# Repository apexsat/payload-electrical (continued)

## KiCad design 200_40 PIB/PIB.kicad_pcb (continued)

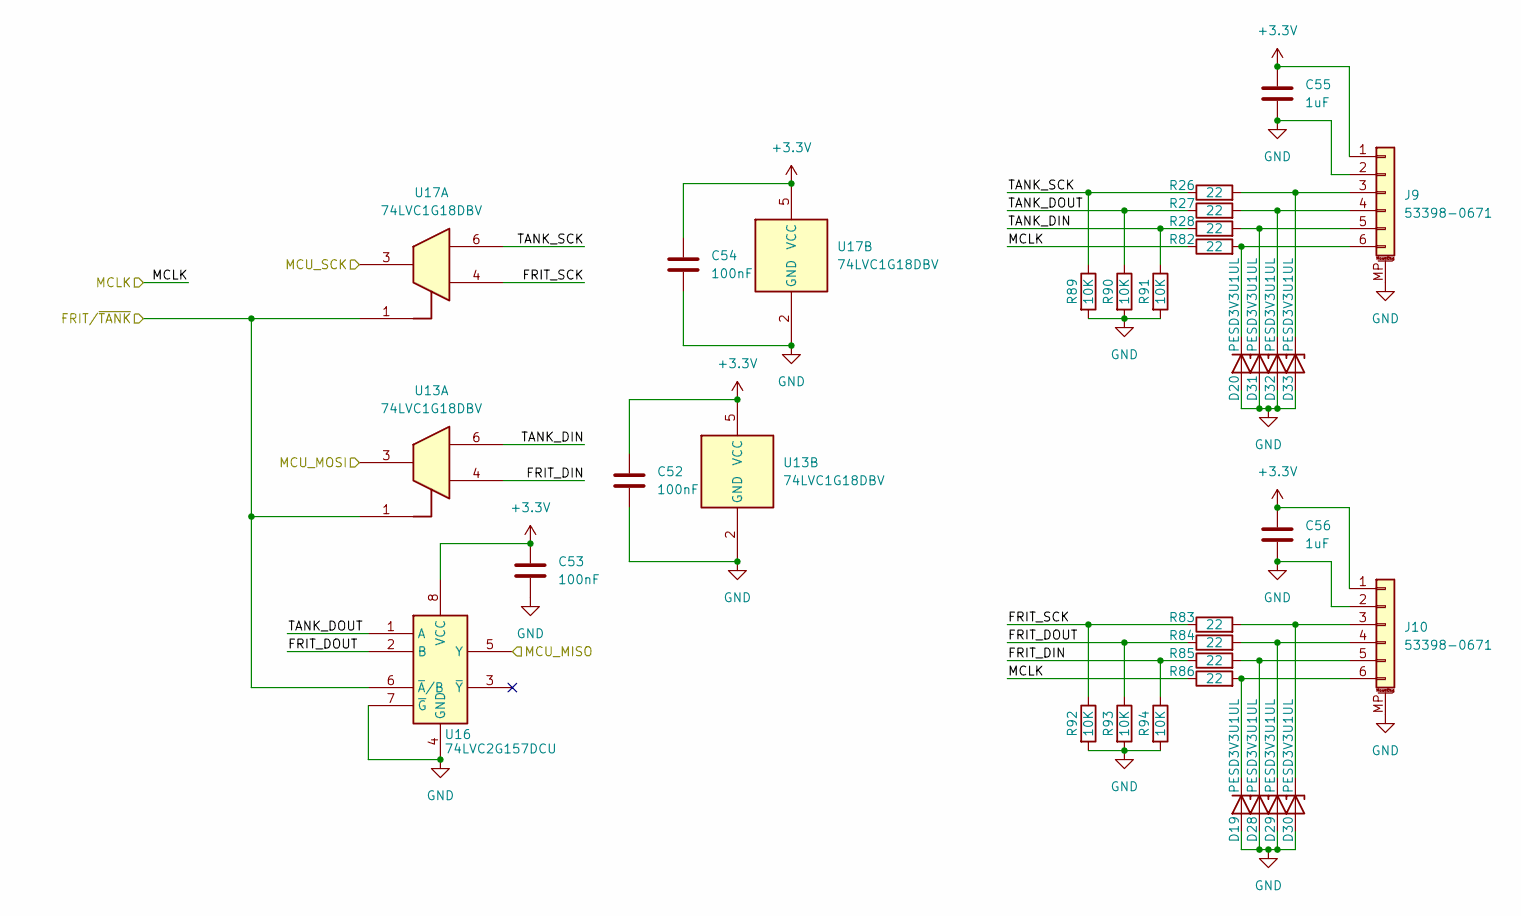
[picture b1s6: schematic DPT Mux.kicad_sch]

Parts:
C52, C53, C54: 100nF; C_0402_1005Metric; Digikey PN 490-10672-1-ND
C55, C56: 1uF; C_0603_1608Metric; Digikey PN 587-3352-1-ND
D19, D20, D28, D29, D30, D31, D32, D33: PESD3V3U1UL; D_SOD-882; Digikey PN 1727-4154-1-ND
J9, J10: 53398-0671; Molex_PicoBlade_53398-0671_1x06-1MP_P1.25mm_Vertical; Digikey PN WM7610CT-ND
R26, R27, R28, R82, R83, R84, R85, R86: 22; R_0402_1005Metric; Digikey PN 311-22.0LRCT-ND
R89, R90, R91, R92, R93, R94: 10K; R_0402_1005Metric; Digikey PN YAG1346CT-ND
U13, U17: 74LVC1G18DBV; SOT-23-6; Digikey PN 296-15568-1-ND
U16: 74LVC2G157DCU; VSSOP-8_2.3x2mm_P0.5mm; Digikey PN 296-12605-1-ND

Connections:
+3.3V: C52.1, C53.1, C54.1, C55.1, C56.1, J9.1, J10.1, U13.5 (VCC), U16.8 (VCC), U17.5 (VCC); also elsewhere on the board
/DPT MUX/FRIT_DIN: R85.1, R94.1, U13.4
/DPT MUX/FRIT_DOUT: R84.1, R93.1, U16.2 (B)
/DPT MUX/FRIT_SCK: R83.1, R92.1, U17.4
/DPT MUX/TANK_DIN: R28.1, R91.1, U13.6
/DPT MUX/TANK_DOUT: R27.1, R90.1, U16.1 (A)
/DPT MUX/TANK_SCK: R26.1, R89.1, U17.6
/DPT_MCLK: R82.1, R86.1; also elsewhere on the board
/FRIT/~TANK: U13.1, U16.6 (~A/B), U17.1; also elsewhere on the board
/INT_SPI_MISO: U16.5 (Y); also elsewhere on the board
/INT_SPI_MOSI: U13.3; also elsewhere on the board
/INT_SPI_SCK: U17.3; also elsewhere on the board
GND: C52.2, C53.2, C54.2, C55.2, C56.2, D19.2 (A), D20.2 (A), D28.2 (A), D29.2 (A), D30.2 (A), D31.2 (A), D32.2 (A), D33.2 (A), J9.2, J9.MP (MountPin), J10.2, J10.MP (MountPin), R89.2, R90.2, R91.2, R92.2, R93.2, R94.2, U13.2 (GND), U16.4 (GND), U16.7 (~G), U17.2 (GND); also elsewhere on the board
unnamed: D19.1 (K), J10.6, R86.2
unnamed: D20.1 (K), J9.6, R82.2
unnamed: D28.1 (K), J10.5, R85.2
unnamed: D29.1 (K), J10.4, R84.2
unnamed: D30.1 (K), J10.3, R83.2
unnamed: D31.1 (K), J9.5, R28.2
unnamed: D32.1 (K), J9.4, R27.2
unnamed: D33.1 (K), J9.3, R26.2

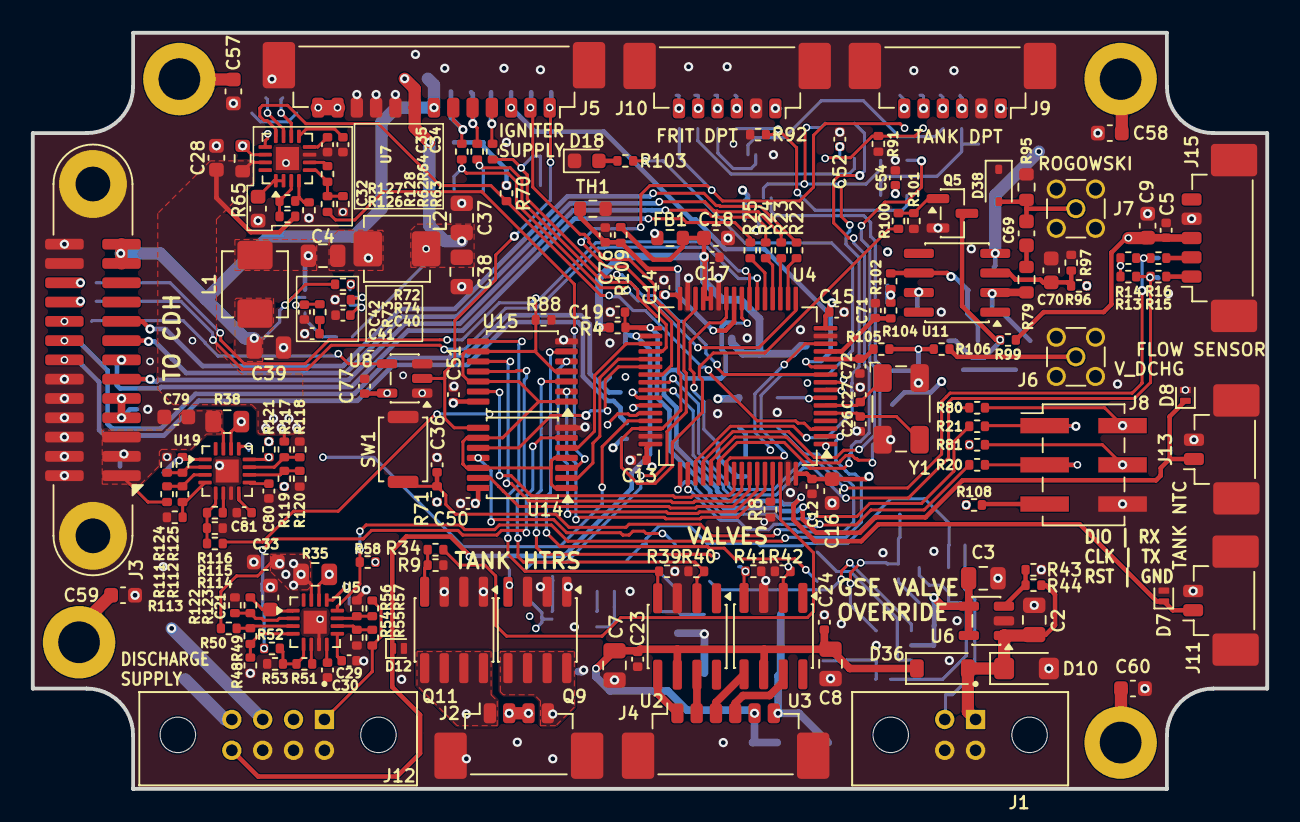
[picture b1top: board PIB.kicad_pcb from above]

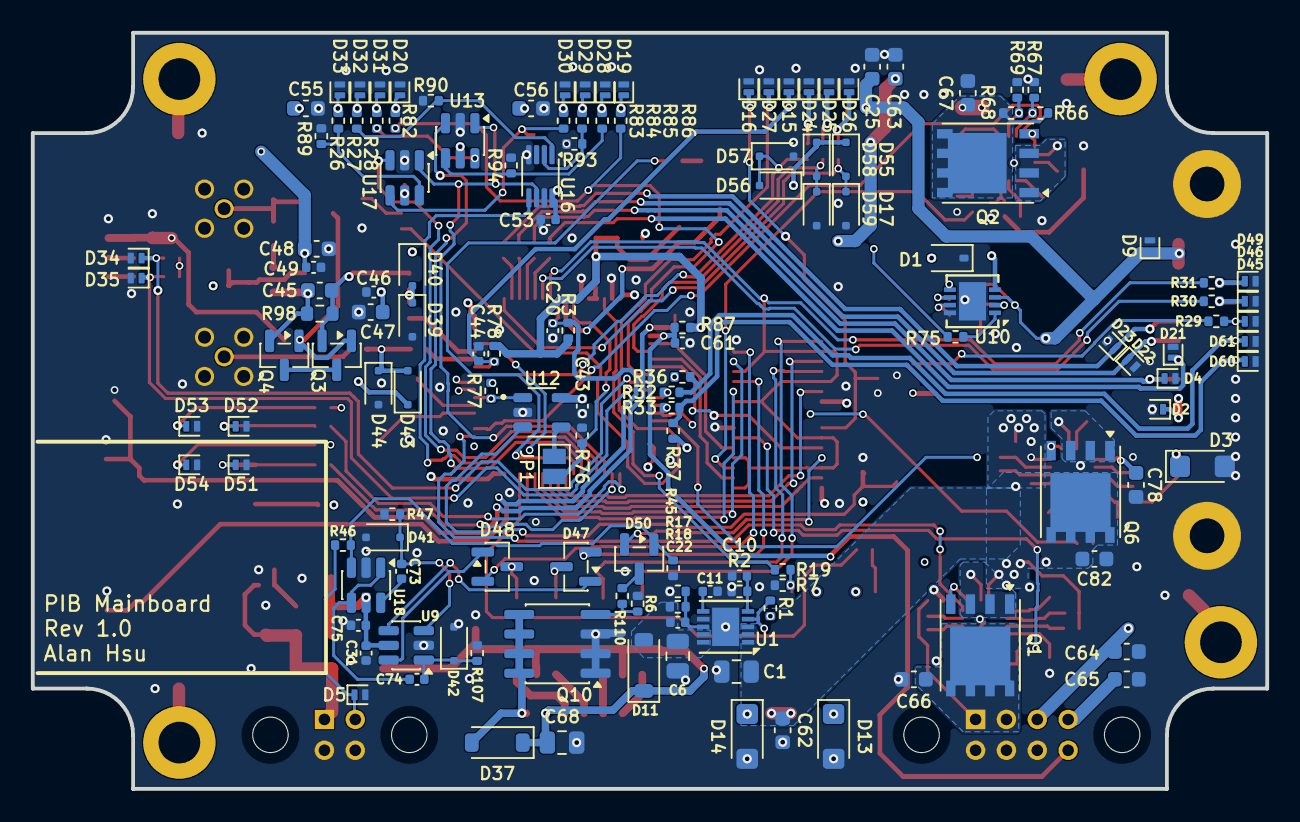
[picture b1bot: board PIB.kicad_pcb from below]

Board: 4 copper layers, 80.0 x 49.0 mm, 319 parts (141 on the bottom side), 192 nets.

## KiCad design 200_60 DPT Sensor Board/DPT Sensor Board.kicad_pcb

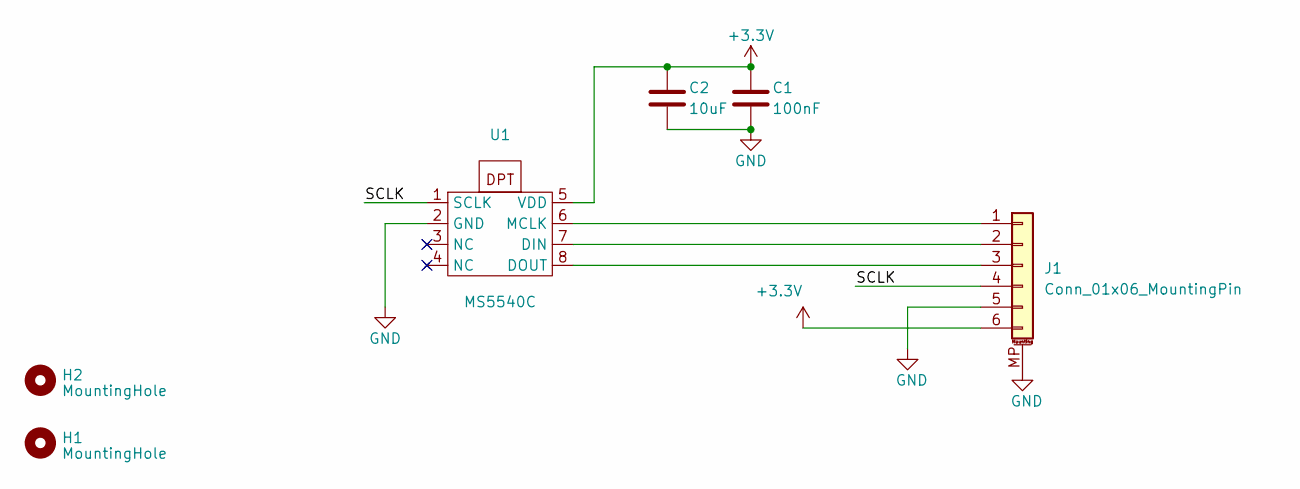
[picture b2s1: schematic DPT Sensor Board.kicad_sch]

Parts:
C1: 100nF; C_0603_1608Metric
C2: 10uF; C_0805_2012Metric
H1, H2: MountingHole; MountingHole_2.1mm
J1: Conn_01x06_MountingPin; Molex_PicoBlade_53261-0671_1x06-1MP_P1.25mm_Horizontal
U1: MS5540C; MPN 325540009-50

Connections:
+3.3V: C1.1, C2.1, J1.6, U1.5 (VDD)
/SCLK: J1.4, U1.1 (SCLK)
GND: C1.2, C2.2, J1.5, J1.MP (MountPin), U1.2 (GND)
unnamed: J1.1, U1.6 (MCLK)
unnamed: J1.2, U1.7 (DIN)
unnamed: J1.3, U1.8 (DOUT)

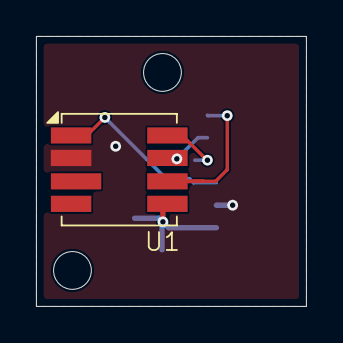
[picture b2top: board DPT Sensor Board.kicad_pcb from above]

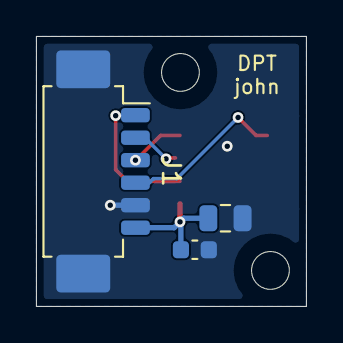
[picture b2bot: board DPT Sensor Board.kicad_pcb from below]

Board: 2 copper layers, 15.0 x 15.0 mm, 6 parts (3 on the bottom side), 6 nets.

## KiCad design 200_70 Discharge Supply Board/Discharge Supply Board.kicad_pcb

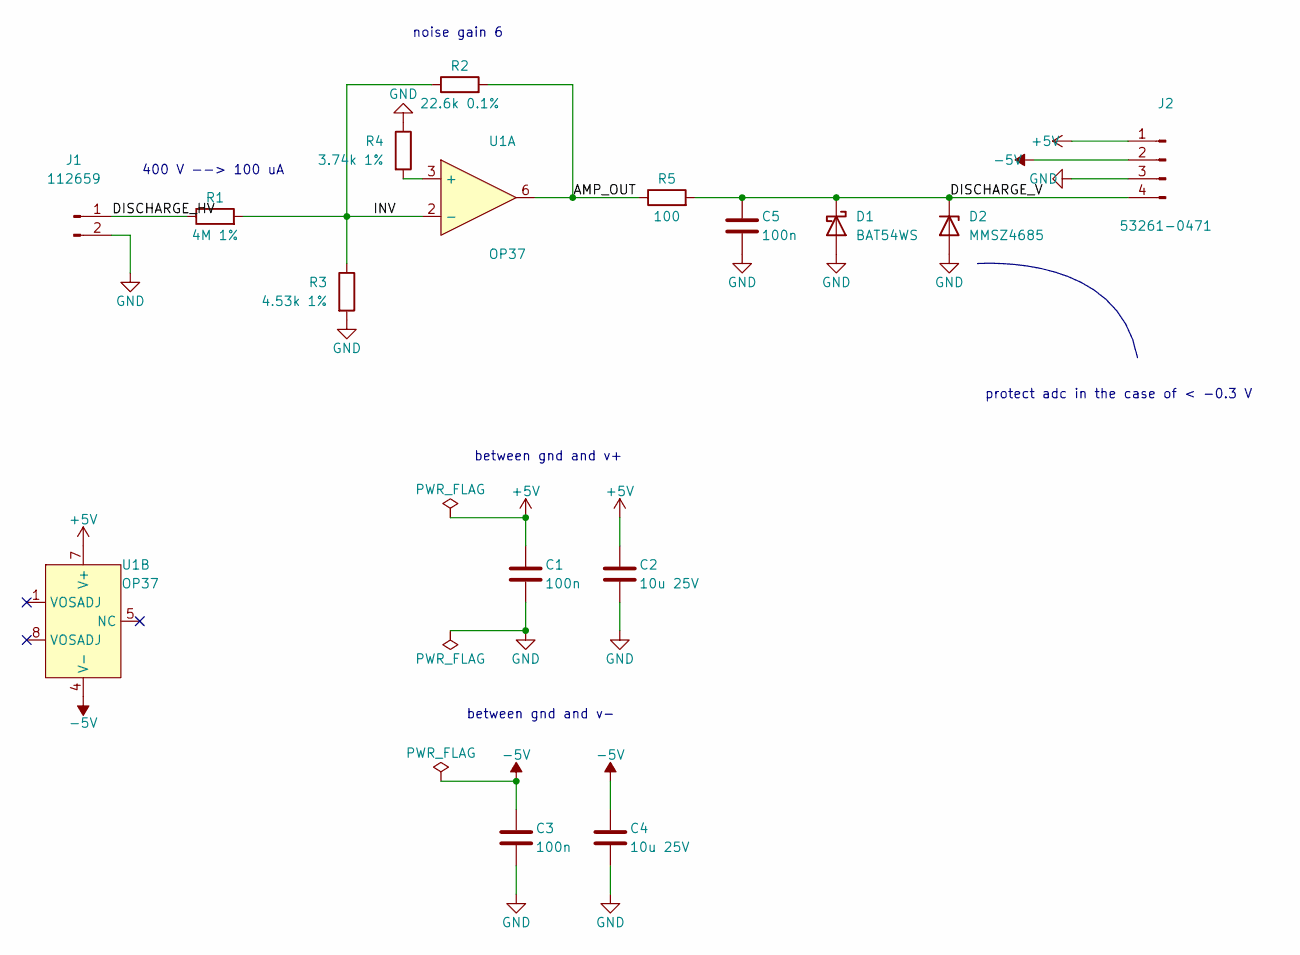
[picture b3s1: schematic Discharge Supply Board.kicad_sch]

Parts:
C1, C3, C5: 100n; C_0603_1608Metric
C2, C4: 10u 25V; C_0805_2012Metric
D1: BAT54WS; D_SOD-323
D2: MMSZ4685; D_SOD-123
J1: 112659; CONN_112659
J2: 53261-0471; Molex_PicoBlade_53261-0471_1x04-1MP_P1.25mm_Horizontal
R1: 4M 1%; R_2512_6332Metric
R2: 22.6k 0.1%; R_0603_1608Metric
R3: 4.53k 1%; R_0603_1608Metric
R4: 3.74k 1%; R_0603_1608Metric
R5: 100; R_0603_1608Metric
U1: OP37; SOIC-8_3.9x4.9mm_P1.27mm

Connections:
+5V: C1.1, C2.1, J2.1, U1.7 (V+)
-5V: C3.1, C4.1, J2.2, U1.4 (V-)
/AMP_OUT: R2.2, R5.1, U1.6
/DISCHARGE_HV: J1.1, R1.1
/DISCHARGE_V: C5.1, D1.1 (K), D2.1 (K), J2.4, R5.2
/INV: R1.2, R2.1, R3.1, U1.2 (-)
GND: C1.2, C2.2, C3.2, C4.2, C5.2, D1.2 (A), D2.2 (A), J1.2, J2.3, R3.2, R4.1
unnamed: R4.2, U1.3 (+)

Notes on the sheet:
protect adc in the case of < -0.3 V
between gnd and v+
400 V --> 100 uA
noise gain 6
between gnd and v-

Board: 2 copper layers, 15 parts (0 on the bottom side), 8 nets, no tracks yet.

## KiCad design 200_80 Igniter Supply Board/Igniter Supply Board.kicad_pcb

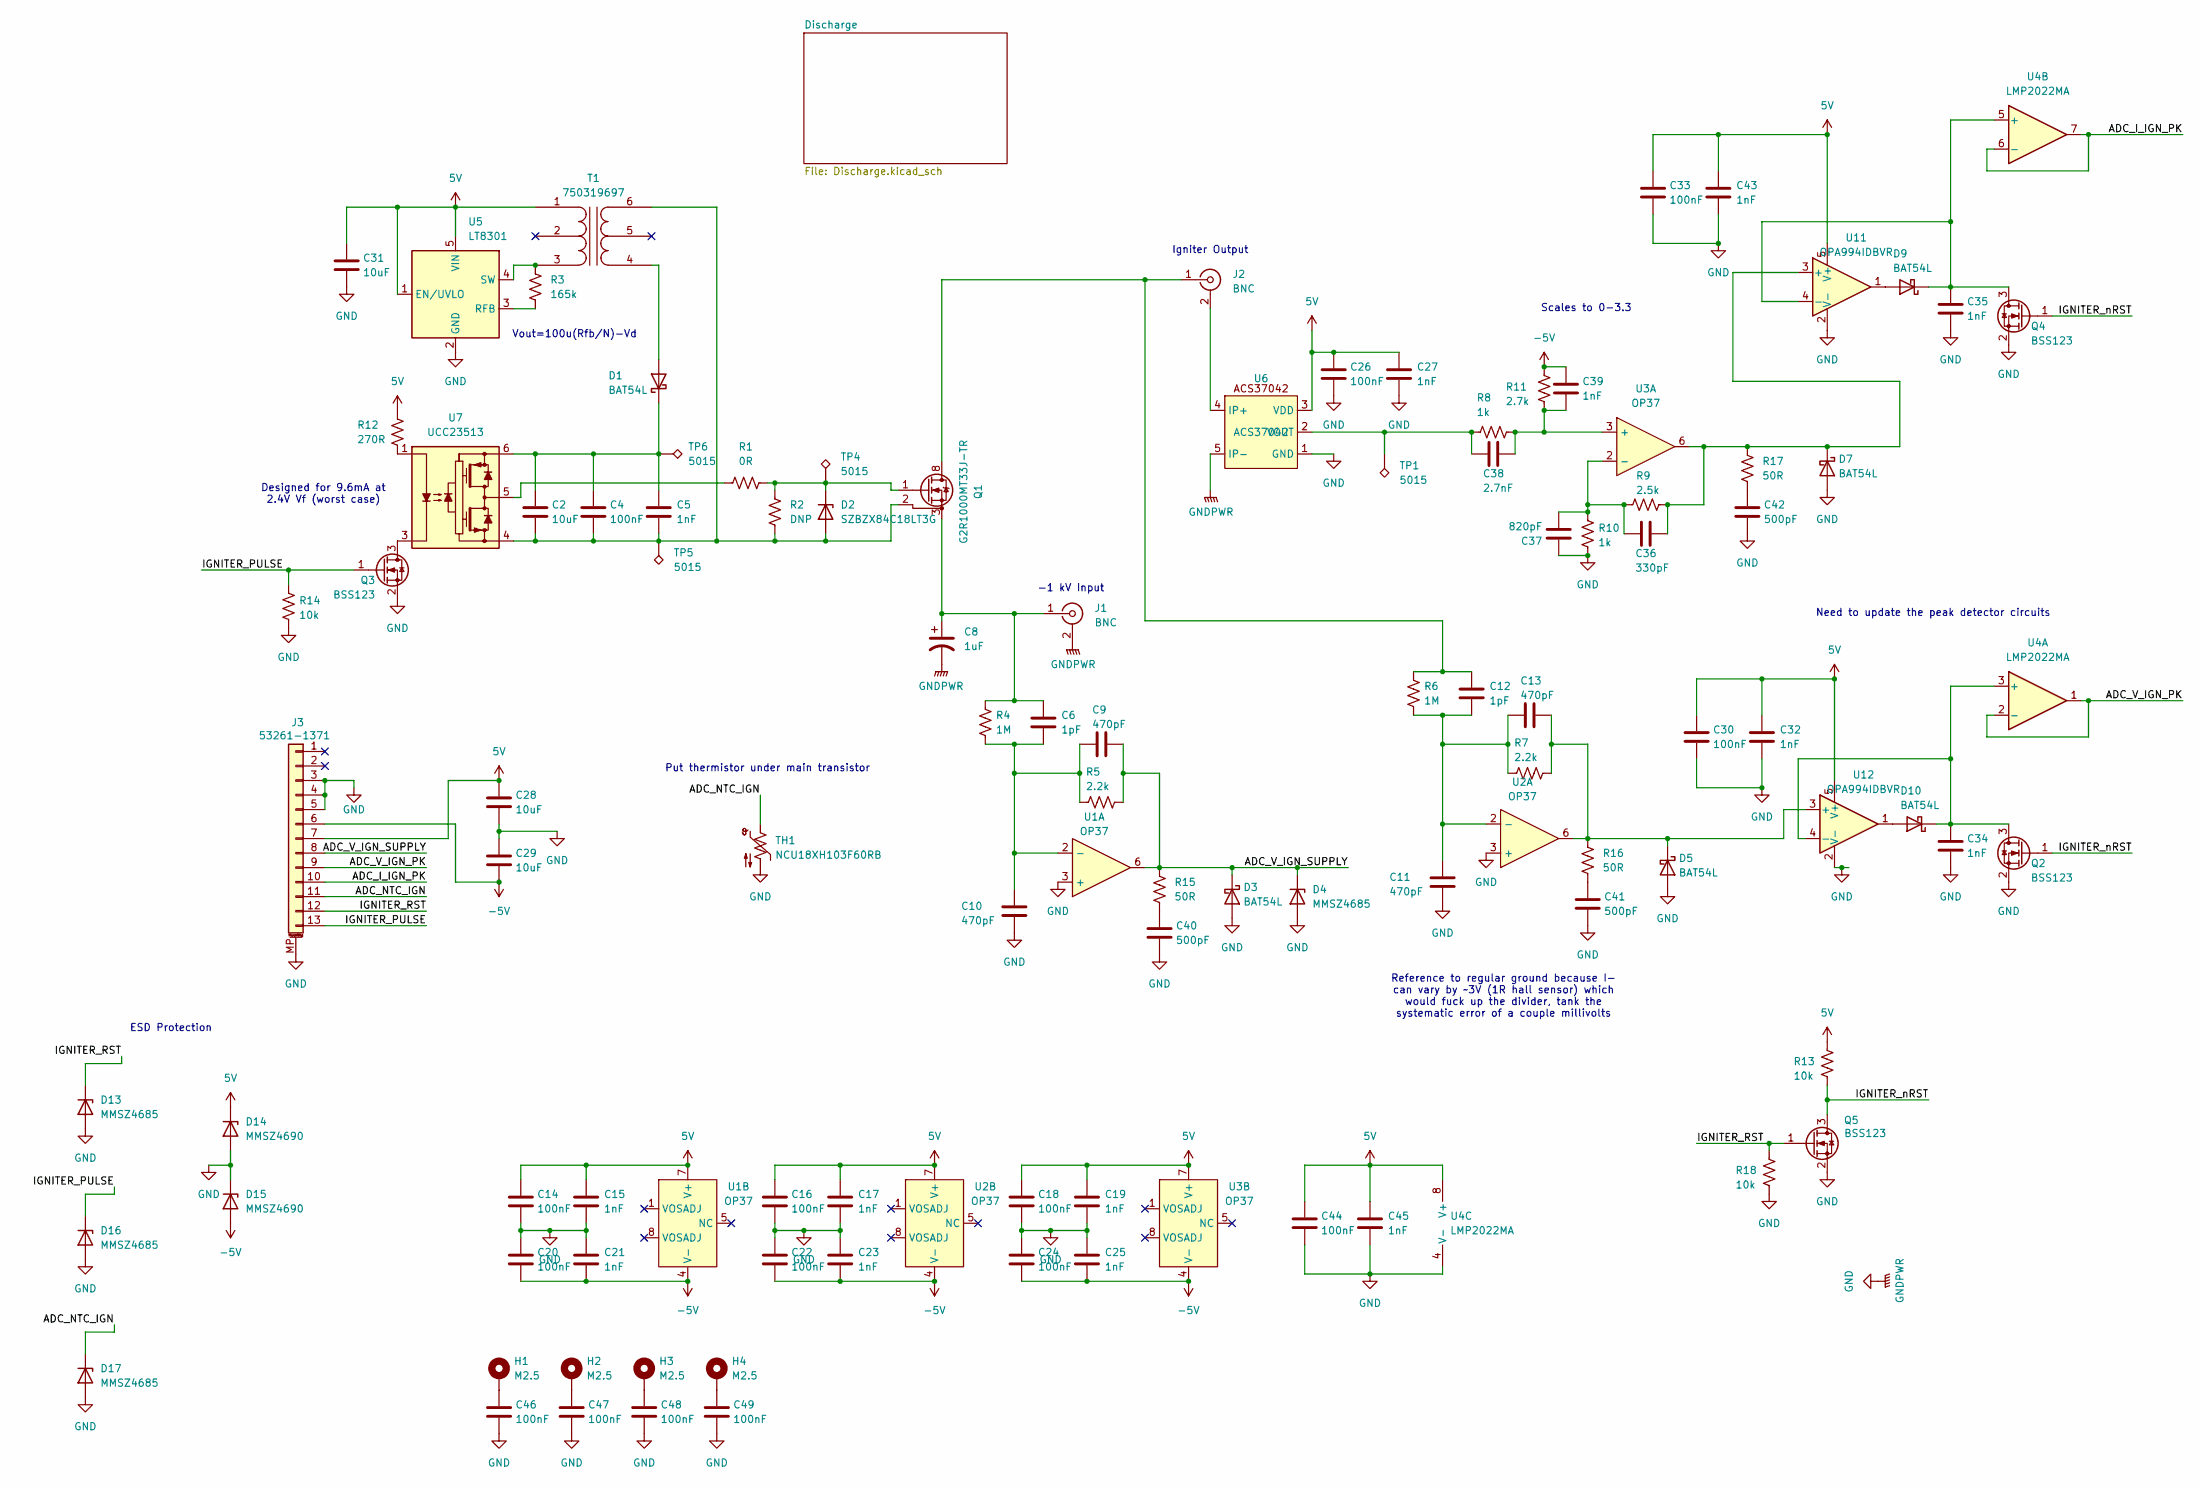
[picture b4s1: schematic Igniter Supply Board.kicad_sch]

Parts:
C2, C28, C29, C31: 10uF; C_1210_3225Metric_Pad1.33x2.70mm_HandSolder; Digikey PN 1276-3387-1-ND
C4, C14, C16, C18, C20, C22, C24, C26, C30, C33, C44, C46, C47, C48, C49: 100nF; C_0603_1608Metric_Pad1.08x0.95mm_HandSolder; Digikey PN 399-C0603C104K5RACTUCT-ND
C5, C15, C17, C19, C21, C23, C25, C27, C32, C34, C35, C39, C43, C45: 1nF; C_0603_1608Metric_Pad1.08x0.95mm_HandSolder; Digikey PN 399-C0603C102F3GACTUCT-ND
C6, C12: 1pF; C_2225_5664Metric_Pad1.80x6.60mm_HandSolder; Digikey PN 1608-1546-1-ND
C8: 1uF; C_Rect_L33.0mm_W20.0mm_P27.50mm_MKS4; Digikey PN 399-C4AQSLU4100A11J-ND
C9, C10, C11, C13: 470pF; C_1206_3216Metric_Pad1.33x1.80mm_HandSolder; Digikey PN 732-12152-1-ND
C36: 330pF; C_0603_1608Metric_Pad1.08x0.95mm_HandSolder; Digikey PN 399-C0603C331F5GACTUCT-ND
C37: 820pF; C_0603_1608Metric_Pad1.08x0.95mm_HandSolder; Digikey PN 490-GCM1885C2A821FA16DCT-ND
C38: 2.7nF; C_0603_1608Metric_Pad1.08x0.95mm_HandSolder; Digikey PN 490-GCM1885C1H272FA16JCT-ND
C40, C41, C42: 500pF; C_0603_1608Metric_Pad1.08x0.95mm_HandSolder; Digikey PN 13-CC0603JRNPO9BN501CT-ND
D1, D3, D5, D7, D9, D10: BAT54L; SOT-23-3; Digikey PN BAT54LT1GOSCT-ND
D2: SZBZX84C18LT3G; SOT-23_Handsoldering; Digikey PN SZBZX84C18LT3GOSCT-ND
D4, D13, D16, D17: MMSZ4685; D_SOD-123; Digikey PN MMSZ4685-TPMSCT-ND
D14, D15: MMSZ4690; D_SOD-123; Digikey PN MMSZ4690-TPMSCT-ND
H1, H2, H3, H4: M2.5; MountingHole_2.7mm_M2.5_DIN965_Pad
J1, J2: BNC; CONN_112659; Digikey PN 115-112659-ND
J3: 53261-1371; Molex_PicoBlade_53398-1371_1x13-1MP_P1.25mm_Vertical; Digikey PN WM14352CT-ND
Q1: G2R1000MT33J-TR; TO-263-7_TabPin8; Digikey PN 1913-G2R1000MT33J-TRCT-ND
Q2, Q3, Q4, Q5: BSS123; SOT-23; Digikey PN BSS123NCT-ND
R1: 0R; R_0603_1608Metric_Pad0.98x0.95mm_HandSolder; Digikey PN 541-2779-1-ND
R2: DNP; R_0603_1608Metric_Pad0.98x0.95mm_HandSolder
R3: 165k; R_0603_1608Metric_Pad0.98x0.95mm_HandSolder; Digikey PN RT0603BRD07165KL
R4, R6: 1M; R_2010_5025Metric_Pad1.40x2.65mm_HandSolder; Digikey PN 2019-HV732HTTE1004FCT-ND
R5, R7: 2.2k; R_1206_3216Metric_Pad1.30x1.75mm_HandSolder; Digikey PN YAG5058CT-ND
R8, R10: 1k; R_0603_1608Metric_Pad0.98x0.95mm_HandSolder; Digikey PN RNCF0603BTE1K00
R9: 2.5k; R_0603_1608Metric_Pad0.98x0.95mm_HandSolder; Digikey PN 738-RNCF0603BTE2K50CT-ND
R11: 2.7k; R_0603_1608Metric_Pad0.98x0.95mm_HandSolder; Digikey PN P20019CT-ND
R12: 270R; R_0603_1608Metric_Pad0.98x0.95mm_HandSolder; Digikey PN 541-10445-1-ND
R13, R14, R18: 10k; R_0603_1608Metric_Pad0.98x0.95mm_HandSolder; Digikey PN RNCF0603BTE10K0CT-ND
R15, R16, R17: 50R; R_0603_1608Metric_Pad0.98x0.95mm_HandSolder; Digikey PN 541-3318-1-ND
T1: 750319697; Transformer_Wuerth_750319697; Digikey PN 1297-750319697CT-ND
TH1: NCU18XH103F60RB; R_0603_1608Metric_Pad0.98x0.95mm_HandSolder; Digikey PN 490-16279-1-ND
TP1, TP4, TP5, TP6: 5015; TestPoint_Keystone_5015_Micro_Mini; Digikey PN 36-5015CT-ND
U1, U2, U3: OP37; SOIC-8_3.9x4.9mm_P1.27mm; Digikey PN 505-OP37GSZ-ND
U4: LMP2022MA; SOIC-8_3.9x4.9mm_P1.27mm; Digikey PN LMP2022MA/NOPB
U5: LT8301; TSOT-23-5_HandSoldering; Digikey PN LT8301ES5#TRMPBF
U6: ACS37042; TSOT-23-5_HandSoldering; Digikey PN 620-ACS37042KLHBLT-010B5CT-ND
U7: UCC23513; SSO-6_6.8x4.6mm_P1.27mm_Clearance8mm; Digikey PN 296-UCC23513QDWYRQ1CT-ND
U11, U12: OPA994IDBVR; TSOT-23-5; Digikey PN 296-OPA994IDBVRCT-ND

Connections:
5V: C14.1, C15.1, C16.1, C17.1, C18.1, C19.1, C26.1, C27.1, C28.1, C30.1, C31.1, C32.1, C33.1, C43.1, C44.1, C45.1, D14.1 (K), J3.7, R12.2, R13.1, T1.1 (PR1), U1.7 (V+), U2.7 (V+), U3.7 (V+), U4.8 (V+), U5.1 (EN/UVLO), U5.5 (VIN), U6.3 (VDD), U11.5 (V+), U12.5 (V+); also elsewhere on the board
-5V: C20.2, C21.2, C22.2, C23.2, C24.2, C25.2, C29.2, C39.1, D15.2 (A), J3.6, R11.1, U1.4 (V-), U2.4 (V-), U3.4 (V-); also elsewhere on the board
/ADC_I_IGN_PK: J3.10, U4.6 (-), U4.7
/ADC_NTC_IGN: D17.1 (K), J3.11, TH1.1
/ADC_V_IGN_PK: J3.9, U4.1, U4.2 (-)
/ADC_V_IGN_SUPPLY: C9.2, D3.3 (K), D4.1 (K), J3.8, R5.1, R15.1, U1.6
/IGNITER_PULSE: D16.1 (K), J3.13, Q3.1 (G), R14.1
/IGNITER_RST: D13.1 (K), J3.12, Q5.1 (G), R18.1
/IGNITER_nRST: Q2.1 (G), Q4.1 (G), Q5.3 (D), R13.2
GND: C8.2, C10.2, C11.2, C14.2, C15.2, C16.2, C17.2, C18.2, C19.2, C20.1, C21.1, C22.1, C23.1, C24.1, C25.1, C26.2, C27.2, C28.2, C29.1, C30.2, C31.2, C32.2, C33.2, C34.2, C35.2, C37.1, C40.2, C41.2, C42.2, C43.2, C44.2, C45.2, C46.2, C47.2, C48.2, C49.2, D3.1 (A), D4.2 (A), D5.1 (A), D7.1 (A), D13.2 (A), D14.2 (A), D15.1 (K), D16.2 (A), D17.2 (A), J1.2 (Ext), J3.3, J3.4, J3.5, J3.MP (MountPin), Q2.2 (S), Q3.2 (S), Q4.2 (S), Q5.2 (S), R10.2, R14.2, R18.2, TH1.2, U1.3 (+), U2.3 (+), U4.4 (V-), U5.2 (GND), U6.1 (GND), U6.5 (IP-), U11.2 (V-), U12.2 (V-); also elsewhere on the board
unnamed: C40.1, R15.2
unnamed: C41.1, R16.2
unnamed: C42.1, R17.2
unnamed: C46.1, H1.1 (1_1)
unnamed: C47.1, H2.1 (1_1)
unnamed: C48.1, H3.1 (1_1)
unnamed: C49.1, H4.1 (1_1)
unnamed: D1.1 (A), T1.4 (S1)
unnamed: C2.1, C4.1, C5.1, D1.3 (K), TP6.1 (1_1), U7.6 (VCC)
unnamed: C2.2, C4.2, C5.2, D2.1 (A), Q1.2 (DS), R2.1, T1.6 (S2), TP5.1 (1_1), U7.4 (VEE)
unnamed: D2.3 (K), Q1.1 (G), R1.2, R2.2, TP4.1 (1_1)
unnamed: C13.2, D5.3 (K), R7.1, R16.1, U2.6, U12.3 (+)
unnamed: C36.1, D7.3 (K), R9.2, R17.1, U3.6, U11.3 (+)
unnamed: D9.1 (A), U11.1
unnamed: C35.1, D9.3 (K), Q4.3 (D), U4.5 (+), U11.4 (-)
unnamed: D10.1 (A), U12.1
unnamed: C34.1, D10.3 (K), Q2.3 (D), U4.3 (+), U12.4 (-)
unnamed: C6.1, C8.1, J1.1 (In), Q1.3 (S), Q1.4 (S), Q1.5 (S), Q1.6 (S), Q1.7 (S), R4.2
unnamed: J2.2 (Ext), U6.4 (IP+)
unnamed: C12.1, J2.1 (In), Q1.8 (D), R6.2
unnamed: Q3.3 (D), U7.3 (C)
unnamed: R3.2, T1.3 (PR2), U5.4 (SW)
unnamed: C6.2, C9.1, C10.1, R4.1, R5.2, U1.2 (-)
unnamed: C11.1, C12.2, C13.1, R6.1, R7.2, U2.2 (-)
unnamed: C38.1, C39.2, R8.1, R11.2, U3.3 (+)
unnamed: C36.2, C37.2, R9.1, R10.1, U3.2 (-)
unnamed: R3.1, U5.3 (RFB)
unnamed: C38.2, R8.2, TP1.1 (1_1), U6.2 (VOUT)
unnamed: R12.1, U7.1 (A)
unnamed: R1.1, U7.5 (VO)

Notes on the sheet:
-1 kV Input
Vout=100u(Rfb/N)-Vd
ESD Protection
Put thermistor under main transistor
Reference to regular ground because I- can vary by ~3V (1R hall sensor) which would fuck up the divider, tank the systematic error of a couple millivolts
Igniter Output
Designed for 9.6mA at 2.4V Vf (worst case)
Need to update the peak detector circuits
Scales to 0-3.3

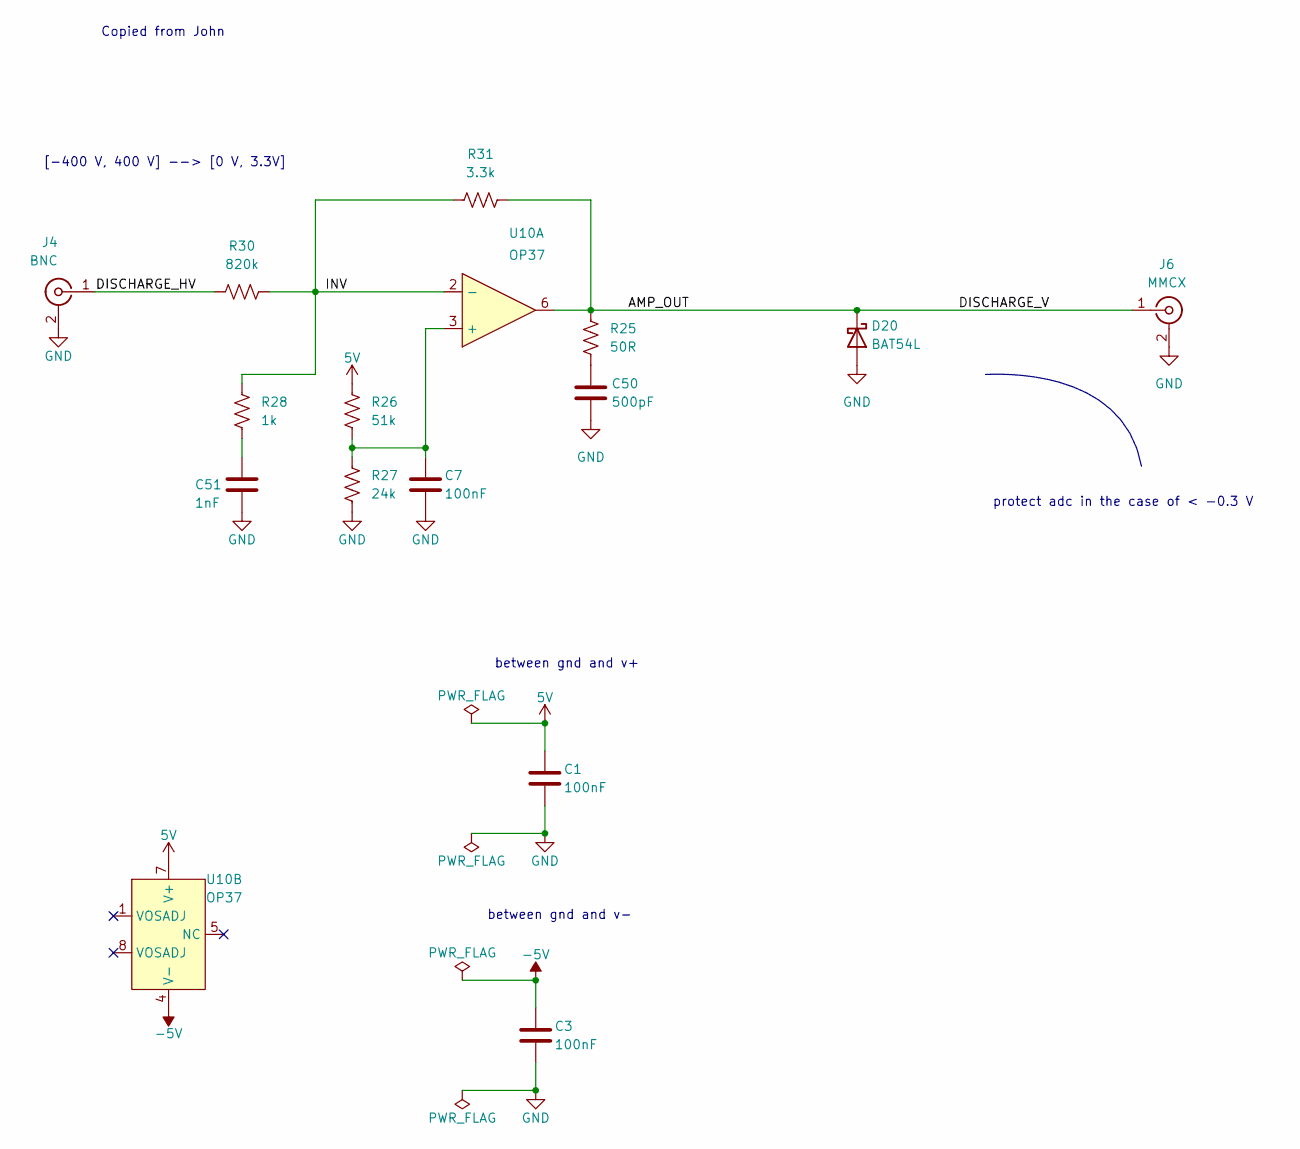
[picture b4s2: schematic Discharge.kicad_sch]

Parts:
C1, C3, C7: 100nF; C_0603_1608Metric_Pad1.08x0.95mm_HandSolder; Digikey PN 399-C0603C104K5RACTUCT-ND
C50: 500pF; C_0603_1608Metric_Pad1.08x0.95mm_HandSolder; Digikey PN 13-CC0603JRNPO9BN501CT-ND
C51: 1nF; C_0603_1608Metric_Pad1.08x0.95mm_HandSolder; Digikey PN 399-C0603C102F3GACTUCT-ND
D20: BAT54L; SOT-23-3; Digikey PN BAT54LT1GOSCT-ND
J4: BNC; CONN_112659; Digikey PN 115-112659-ND
J6: MMCX; MMCX_Molex_73415-1471_Vertical; Digikey PN WM5557-ND
R25: 50R; R_0603_1608Metric_Pad0.98x0.95mm_HandSolder; Digikey PN 541-3318-1-ND
R26: 51k; R_0603_1608Metric_Pad0.98x0.95mm_HandSolder; Digikey PN RR08P51.0KDCT-ND
R27: 24k; R_0603_1608Metric_Pad0.98x0.95mm_HandSolder; Digikey PN RG16P24.0KBCT-ND
R28: 1k; R_0603_1608Metric_Pad0.98x0.95mm_HandSolder; Digikey PN RNCF0603BTE1K00
R30: 820k; R_2512_6332Metric; Digikey PN A130028CT-ND
R31: 3.3k; R_0603_1608Metric_Pad0.98x0.95mm_HandSolder; Digikey PN P123763CT-ND
U10: OP37; SOIC-8_3.9x4.9mm_P1.27mm; Digikey PN 505-OP37GSZ-ND

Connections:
5V: C1.1, R26.1, U10.7 (V+); also elsewhere on the board
-5V: C3.1, U10.4 (V-); also elsewhere on the board
/Discharge/AMP_OUT: D20.3 (K), J6.1 (In), R25.1, R31.2, U10.6
/Discharge/DISCHARGE_HV: J4.1 (In), R30.1
/Discharge/INV: R28.1, R30.2, R31.1, U10.2 (-)
GND: C1.2, C3.2, C7.2, C50.2, C51.1, D20.1 (A), J4.2 (Ext), J6.2 (Ext), R27.2; also elsewhere on the board
unnamed: C50.1, R25.2
unnamed: C51.2, R28.2
unnamed: C7.1, R26.2, R27.1, U10.3 (+)

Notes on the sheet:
between gnd and v-
[-400 V, 400 V] --> [0 V, 3.3V]
Copied from John
protect adc in the case of < -0.3 V
between gnd and v+

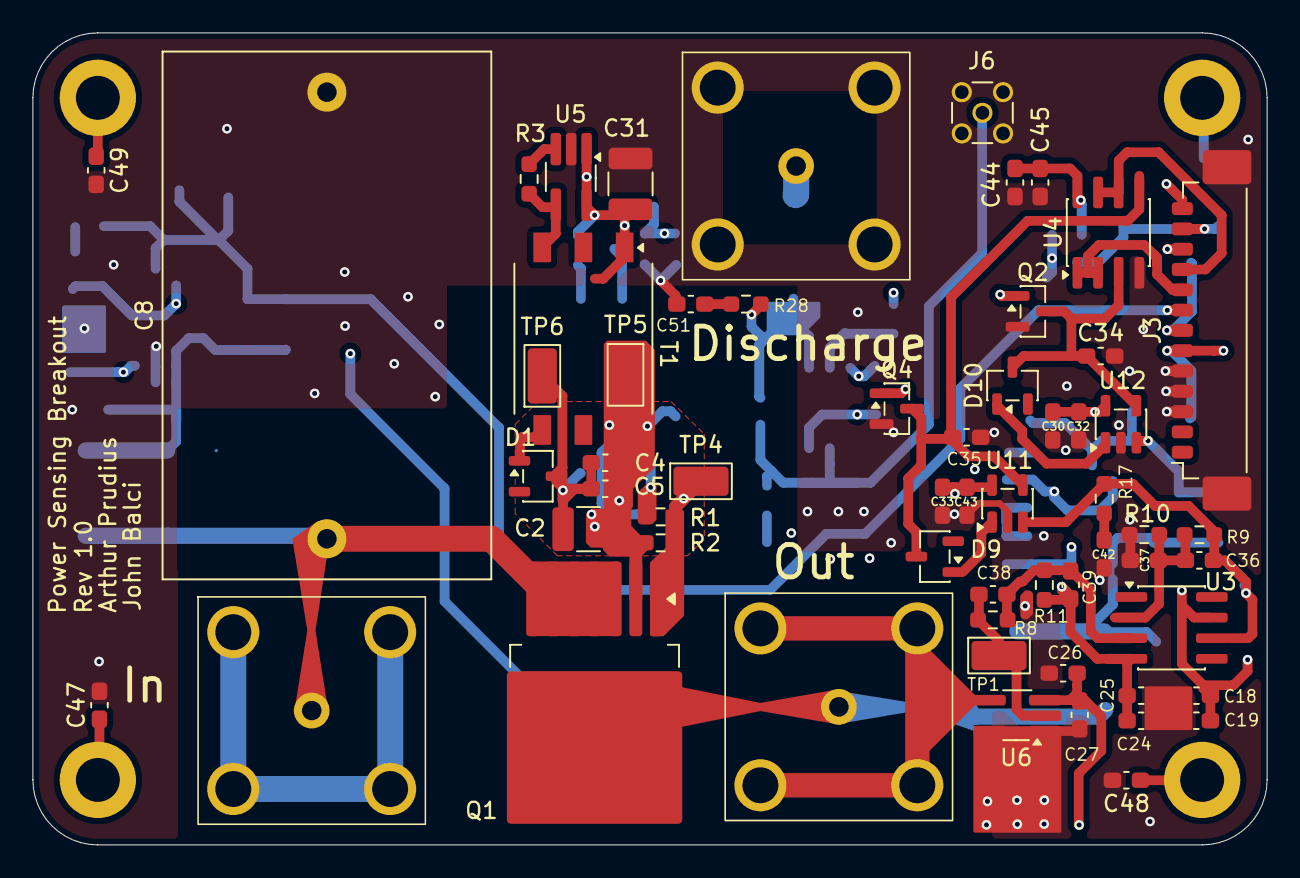
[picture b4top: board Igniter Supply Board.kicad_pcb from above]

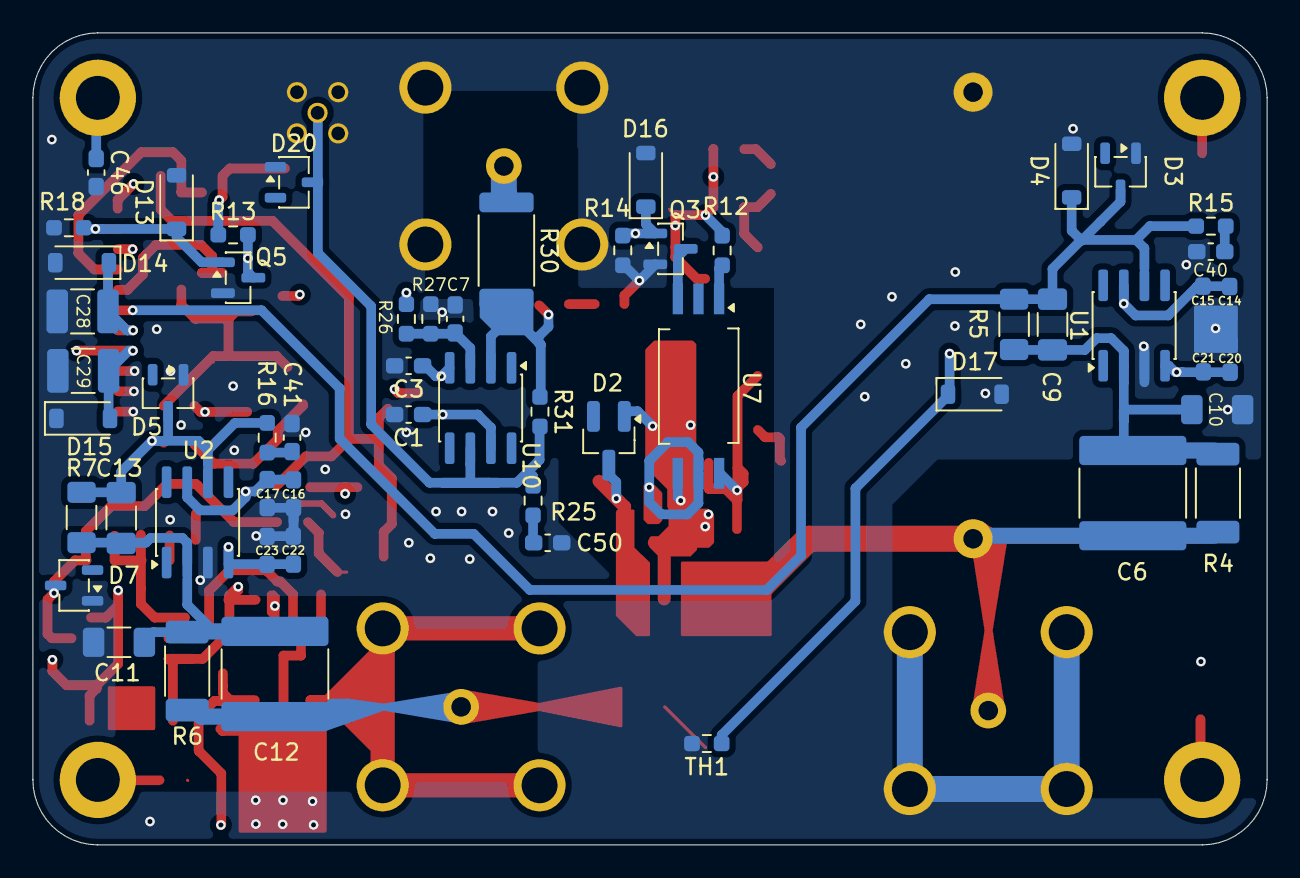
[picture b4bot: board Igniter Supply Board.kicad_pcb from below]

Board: 4 copper layers, 76.0 x 50.0 mm, 119 parts (56 on the bottom side), 46 nets.

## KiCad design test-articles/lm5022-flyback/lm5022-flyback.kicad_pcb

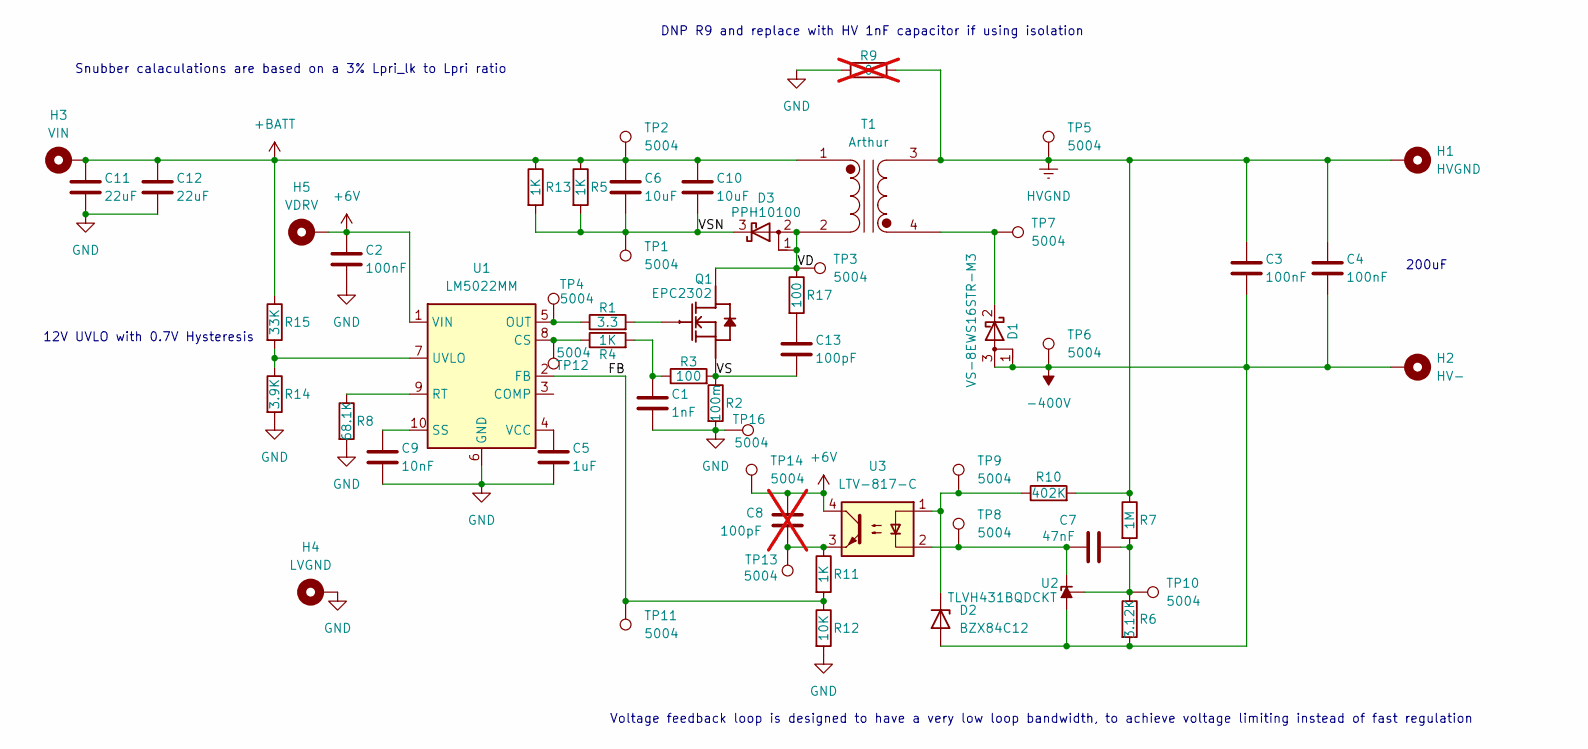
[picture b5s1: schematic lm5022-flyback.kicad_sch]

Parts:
C1: 1nF; C_0402_1005Metric
C2: 100nF; C_0402_1005Metric
C3, C4: 100nF; C_2220_5750Metric
C5: 1uF; C_0402_1005Metric
C6, C10: 10uF; C_1210_3225Metric
C7: 47nF; C_0603_1608Metric
C8: 100pF; C_0603_1608Metric; not fitted
C9: 10nF; C_0402_1005Metric
C11, C12: 22uF; C_1210_3225Metric
C13: 100pF; C_0603_1608Metric
D1: VS-8EWS16STR-M3; TO-252-2
D2: BZX84C12; SOT-23
D3: PPH10100; TO-277A
H1: HVGND; Pad6x4
H2: HV-; Pad6x4
H3: VIN; Pad6x4
H4: LVGND; Pad6x4
H5: VDRV; Pad6x4
Q1: EPC2302; D0606F_100V
R1: 3.3; R_0402_1005Metric
R2: 100m; R_1225_3264Metric
R3: 100; R_0402_1005Metric
R4: 1K; R_0402_1005Metric
R5, R13: 1K; R_0805_2012Metric
R6: 3.12K; R_0603_1608Metric
R7: 1M; R_2512_6332Metric
R8: 68.1K; R_0402_1005Metric
R9: 0; R_2010_5025Metric; not fitted
R10: 402K; R_2512_6332Metric
R11: 1K; R_0603_1608Metric
R12: 10K; R_0603_1608Metric
R14: 3.9K; R_0603_1608Metric
R15: 33K; R_0603_1608Metric
R17: 100; R_0603_1608Metric
T1: Arthur; 40-2Transformer
TP1, TP2, TP3, TP4, TP5, TP6, TP7, TP8, TP9, TP10, TP11, TP12, TP13, TP14, TP16: 5004; TestPoint_Keystone_5000-5004_Miniature
U1: LM5022MM; MSOP-10_3x3mm_P0.5mm
U2: TLVH431BQDCKT; SOT-363_SC-70-6
U3: LTV-817-C; DIP-4_W7.62mm

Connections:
+6V: C2.1, C8.2, H5.1, TP14.1, U1.1 (VIN), U3.4
+BATT: C6.1, C10.1, C11.1, C12.1, H3.1, R5.1, R13.1, R15.1, T1.1 (AA), TP2.1
-400V: C3.2, C4.2, D1.1 (A), D1.3 (A), D2.1 (A), H2.1, R6.2, TP6.1, U2.6 (A)
/FB: R11.2, R12.1, TP11.1, U1.2 (FB)
/VD: D3.1 (A), D3.2 (A), Q1.3 (D), Q1.5 (D), Q1.7 (D), R17.1, T1.2 (AB), TP3.1
/VS: C13.2, Q1.2 (S), Q1.4 (S), Q1.6 (S), R2.1, R3.2
/VSN: C6.2, C10.2, D3.3 (K), R5.2, R13.2, TP1.1
GND: C1.2, C2.2, C5.2, C9.2, C11.2, C12.2, H4.1, R2.2, R8.2, R9.1, R12.2, R14.2, TP16.1, U1.6 (GND)
HVGND: C3.1, C4.1, H1.1, R7.1, R9.2, R10.2, T1.3 (SA), TP5.1
unnamed: C1.1, R3.1, R4.2
unnamed: C8.1, R11.1, TP13.1, U3.3
unnamed: C13.1, R17.2
unnamed: D1.2 (K), T1.4 (SB), TP7.1
unnamed: D2.3 (K), R10.1, TP9.1, U3.1
unnamed: Q1.1 (G), R1.2
unnamed: R4.1, TP12.1, U1.8 (CS)
unnamed: R1.1, TP4.1, U1.5 (OUT)
unnamed: R8.1, U1.9 (RT)
unnamed: C9.1, U1.10 (SS)
unnamed: R14.1, R15.2, U1.7 (UVLO)
unnamed: C5.1, U1.4 (VCC)
unnamed: C7.1, TP8.1, U2.1 (K), U3.2
unnamed: C7.2, R6.1, R7.2, TP10.1, U2.3 (REF)

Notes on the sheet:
DNP R9 and replace with HV 1nF capacitor if using isolation
200uF
Snubber calaculations are based on a 3% Lpri_lk to Lpri ratio
12V UVLO with 0.7V Hysteresis
Voltage feedback loop is designed to have a very low loop bandwidth, to achieve voltage limiting instead of fast regulation
